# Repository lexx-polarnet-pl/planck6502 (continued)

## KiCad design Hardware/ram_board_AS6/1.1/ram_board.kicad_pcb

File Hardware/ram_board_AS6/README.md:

## Planck 6502 AS6 RAM board

This is a banked RAM board for the Planck 6502 computer (AS6C4008-55PCN version).

The original project used the IS61C5128AL-10TLI, which was hard for me to obtain and was an SMD version. The AS6 is THT, so the soldering process should be much easier.

## Revision History

| Version | Status | Changes |
| :---: | :---: | :--- |
| **1.1** | Work in progress | WE signal is now active only when CPU operates in RAM expansion card window |
| **1.0** | Partially working | Forked from original banked RAM project, replacing IS6 with AS6 |

**Version 1.0 doesn't work correctly, version 1.1 was not tested yet**

The address decoder in this version is used only for OE; therefore, the card works properly in READ mode. However, it is not used to control WE signals. As a result, if the CPU wants to write a value into a memory area that should be out of range for this card (e.g., $0080), the value will be stored both in main RAM (at $0080) and in banked RAM (at $8080).

How it should work:

When active, it gives access to a bank or RAM in the $8000-$BFFF address space.

To activate, store a byte with it's high bit set to the first register of the slot where it is placed.

For example 
lda #$80
sta $FFD0
will activate bank 0

There are 32 banks. You can choose which one is active by setting the first 5 bits of the data when storing to the first register. There is no way to get the currently active bank.

When the RAM card is active, it will respond to requests in the $8000 to $BFFF range instead of the ROM

lda #$8E
sta $FFD0
will activate the 14th bank

Setting the high bit to 0 will deactivate the banked RAM

For example the following code will deactivate the banked RAM and restore the ROM :

lda #0
sta $FFD0

<br />This documentation is licensed under a <a rel="license" href="http://creativecommons.org/licenses/by-sa/4.0/">Creative Commons Attribution-ShareAlike 4.0 International License</a>.

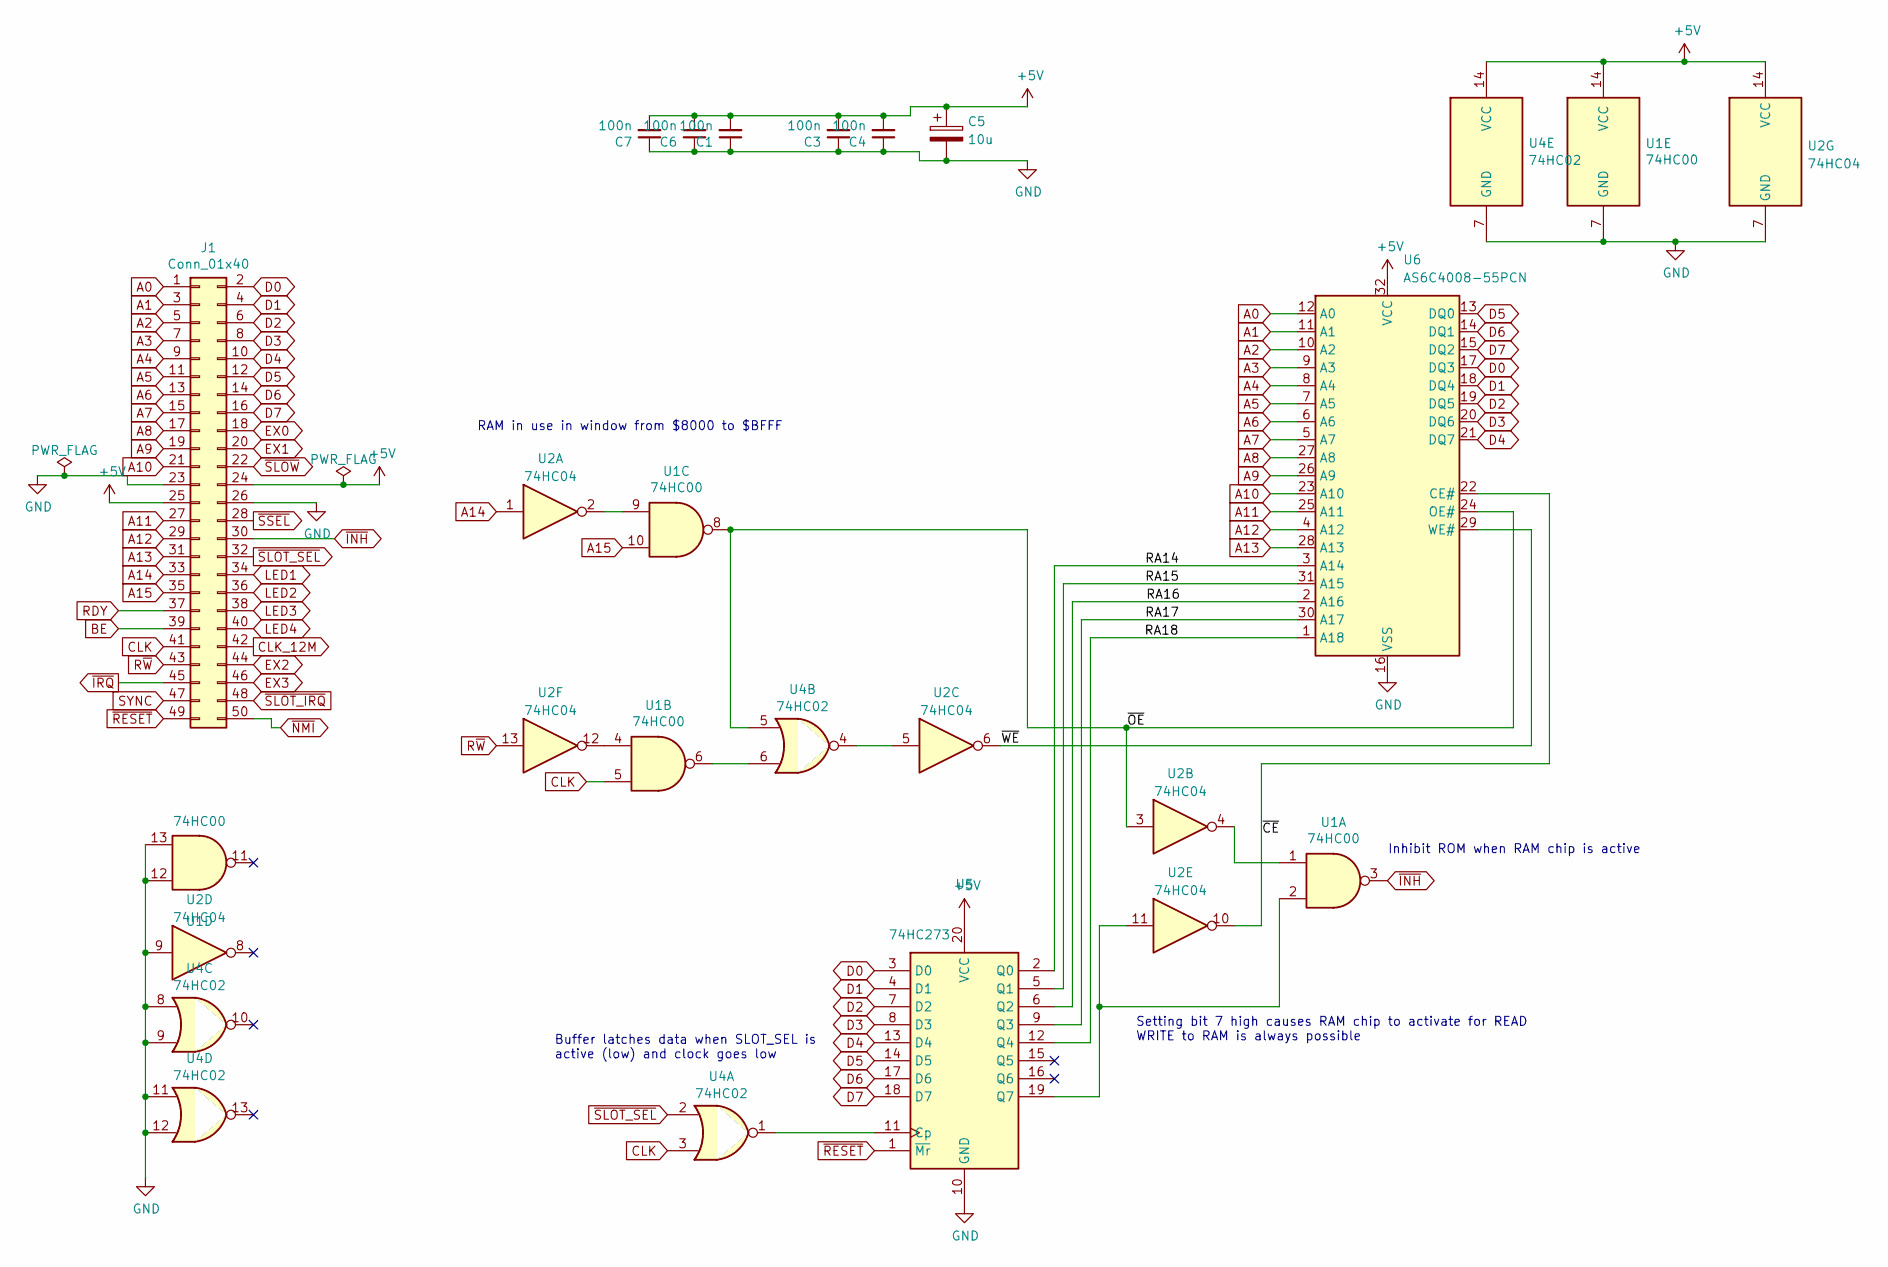
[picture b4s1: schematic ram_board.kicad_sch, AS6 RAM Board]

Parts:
C1, C3, C4, C6, C7: 100n; C_Disc_D4.3mm_W1.9mm_P5.00mm
C5: 10u; C_Radial_D5.0mm_H11.0mm_P2.00mm
J1: Conn_01x40; PinHeader_2x25_P2.54mm_Horizontal
U1: 74HC00; DIP-14_W7.62mm_Socket
U2: 74HC04; DIP-14_W7.62mm_Socket
U4: 74HC02; DIP-14_W7.62mm_Socket
U5: 74HC273; DIP-20_W7.62mm_Socket
U6: AS6C4008-55PCN; DIP-32_W15.24mm_Socket

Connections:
+5V: C1.2, C3.2, C4.2, C5.1, C6.2, C7.2, J1.24, J1.25, U1.14 (VCC), U2.14 (VCC), U4.14 (VCC), U5.20 (VCC), U6.32 (VCC)
/RA14: U5.2 (Q0), U6.3 (A14)
/RA15: U5.5 (Q1), U6.31 (A15)
/RA16: U5.6 (Q2), U6.2 (A16)
/RA17: U5.9 (Q3), U6.30 (A17)
/RA18: U5.12 (Q4), U6.1 (A18)
/~CE: U2.10, U6.22 (CE#)
/~OE: U1.8, U2.3, U4.5, U6.24 (OE#)
/~WE: U2.6, U6.29 (WE#)
A0: J1.1, U6.12 (A0)
A1: J1.3, U6.11 (A1)
A2: J1.5, U6.10 (A2)
A3: J1.7, U6.9 (A3)
A4: J1.9, U6.8 (A4)
A5: J1.11, U6.7 (A5)
A6: J1.13, U6.6 (A6)
A7: J1.15, U6.5 (A7)
A8: J1.17, U6.27 (A8)
A9: J1.19, U6.26 (A9)
A10: J1.21, U6.23 (A10)
A11: J1.27, U6.25 (A11)
A12: J1.29, U6.4 (A12)
A13: J1.31, U6.28 (A13)
A14: J1.33, U2.1
A15: J1.35, U1.10
BE: J1.39
CLK: J1.41, U1.5, U4.3
CLK_12M: J1.42
D0: J1.2, U5.3 (D0), U6.17 (DQ3)
D1: J1.4, U5.4 (D1), U6.18 (DQ4)
D2: J1.6, U5.7 (D2), U6.19 (DQ5)
D3: J1.8, U5.8 (D3), U6.20 (DQ6)
D4: J1.10, U5.13 (D4), U6.21 (DQ7)
D5: J1.12, U5.14 (D5), U6.13 (DQ0)
D6: J1.14, U5.17 (D6), U6.14 (DQ1)
D7: J1.16, U5.18 (D7), U6.15 (DQ2)
EX0: J1.18
EX1: J1.20
EX2: J1.44
EX3: J1.46
GND: C1.1, C3.1, C4.1, C5.2, C6.1, C7.1, J1.23, J1.26, U1.7 (GND), U1.12, U1.13, U2.7 (GND), U2.9, U4.7 (GND), U4.8, U4.9, U4.11, U4.12, U5.10 (GND), U6.16 (VSS)
LED1: J1.34
LED2: J1.36
LED3: J1.38
LED4: J1.40
unnamed: U1.1, U2.4
unnamed: U1.4, U2.12
unnamed: U1.6, U4.6
unnamed: U1.9, U2.2
unnamed: U2.5, U4.4
unnamed: U4.1, U5.11 (Cp)
unnamed: U1.2, U2.11, U5.19 (Q7)
RDY: J1.37
R~W: J1.43, U2.13
SYNC: J1.47
~INH: J1.30, U1.3
~IRQ: J1.45
~NMI: J1.50
~RESET: J1.49, U5.1 (~Mr)
~SLOT_IRQ: J1.48
~SLOT_SEL: J1.32, U4.2
~SLOW: J1.22
~SSEL: J1.28

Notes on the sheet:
Inhibit ROM when RAM chip is active
RAM in use in window from $8000 to $BFFF
Buffer latches data when SLOT_SEL is active (low) and clock goes low
Setting bit 7 high causes RAM chip to activate for READ WRITE to RAM is always possible

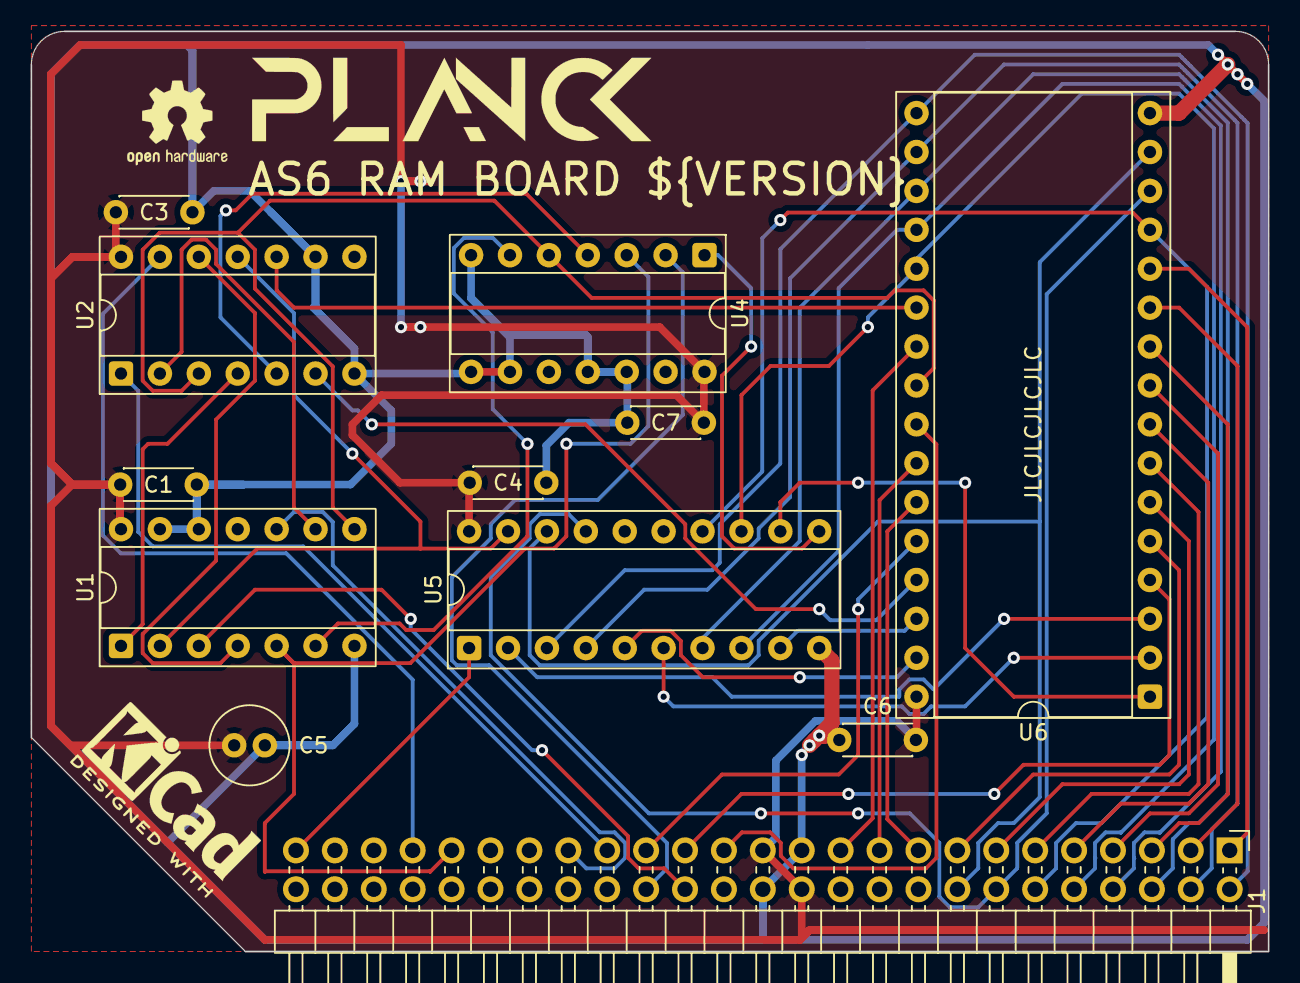
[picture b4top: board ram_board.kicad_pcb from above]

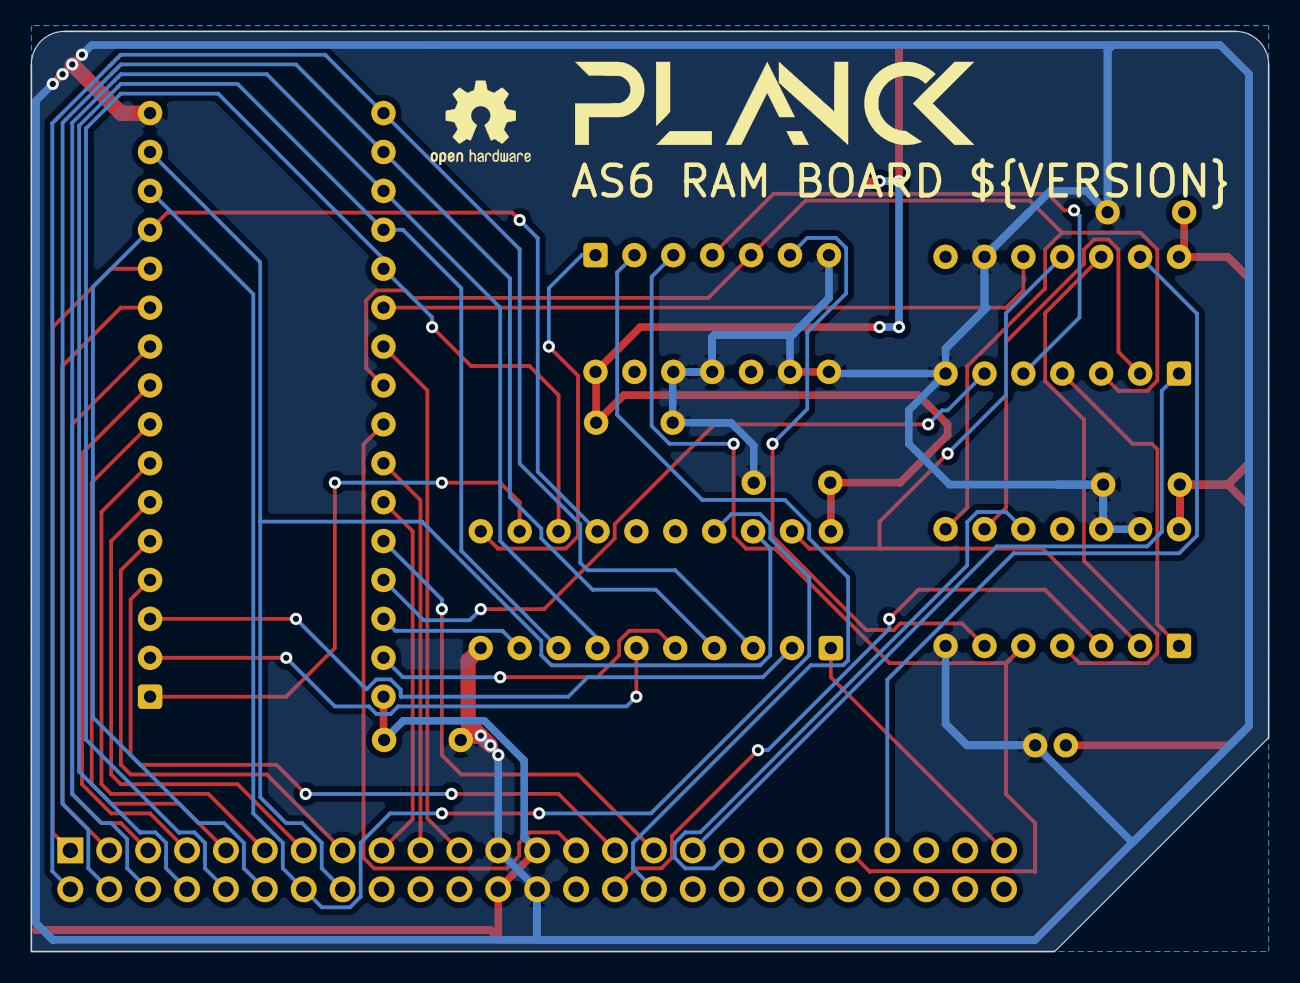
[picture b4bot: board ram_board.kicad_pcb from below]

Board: 2 copper layers, 80.8 x 60.1 mm, 16 parts (2 on the bottom side), 46 nets.

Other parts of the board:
LOGO, LOGO2: LOGO; logo
OSHW1, OSHW2: OSHW-Logo2_7.3x6mm_SilkScreen

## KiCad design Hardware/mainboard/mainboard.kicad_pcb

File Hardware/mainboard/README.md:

## Planck computer

This is a modified version of the original Planck mainboard, featuring a small addition that enables clock stretching for the serial interface.

Since the original design uses the W65C51 for serial communication and I had some R6551 chips on hand, I wanted to be able to use them instead. The pinout for both chips is identical; however, the R6551 can only run at a maximum of 2 MHz (depending on the version), so it cannot operate at the full CPU clock speed. With this additional jumper, it is possible to lower the clock frequency for the ACIA. Note that the main clock must be set to a maximum of 8 MHz, as the clock stretching circuit can divide the frequency by up to 4 times (meaning an original 12 MHz clock would yield 3 MHz during stretching, which is still too high for the R6551). The remainder of the design is identical to the original version.

## Revision History

| Version | Status | Changes |
| :---: | :---: | :--- |
| **1.4.9-Lexx** | Working | Forked from the project; added JP5 jumper to enable clock stretching for serial |

**This version is tested and working.**

Below is the original documentation excerpt:

This is a complete computer based on the Planck 6502 backplane.

It provides a 65c02 cPU, 32k of RAM, 32k of ROM and a serial port, as well as 6 expansion slots.

The board exceeds the original size specification of the original project (100 x 150mm instead of 100 x 100mm) but it seems that the cost will be similar (one more expensive board replaces 3 cheaper boards) as well as being more practical for some applications.

This computer can run absolutely stand alone when connected via the serial port. It can also accommodate 2 more expansion cards compared to the original backplane.

Here is a 3D view of the board:

You can [download the schematic](https://planck6502.com/fabrication/mainboard-schematic.pdf) and the [gerber files](https://planck6502.com/fabrication/mainboard-zip.zip)

[Documentation](https://planck6502.com/Hardware/io/)

<br />This documentation is licensed under a <a rel="license" href="http://creativecommons.org/licenses/by-sa/4.0/">Creative Commons Attribution-ShareAlike 4.0 International License</a>.

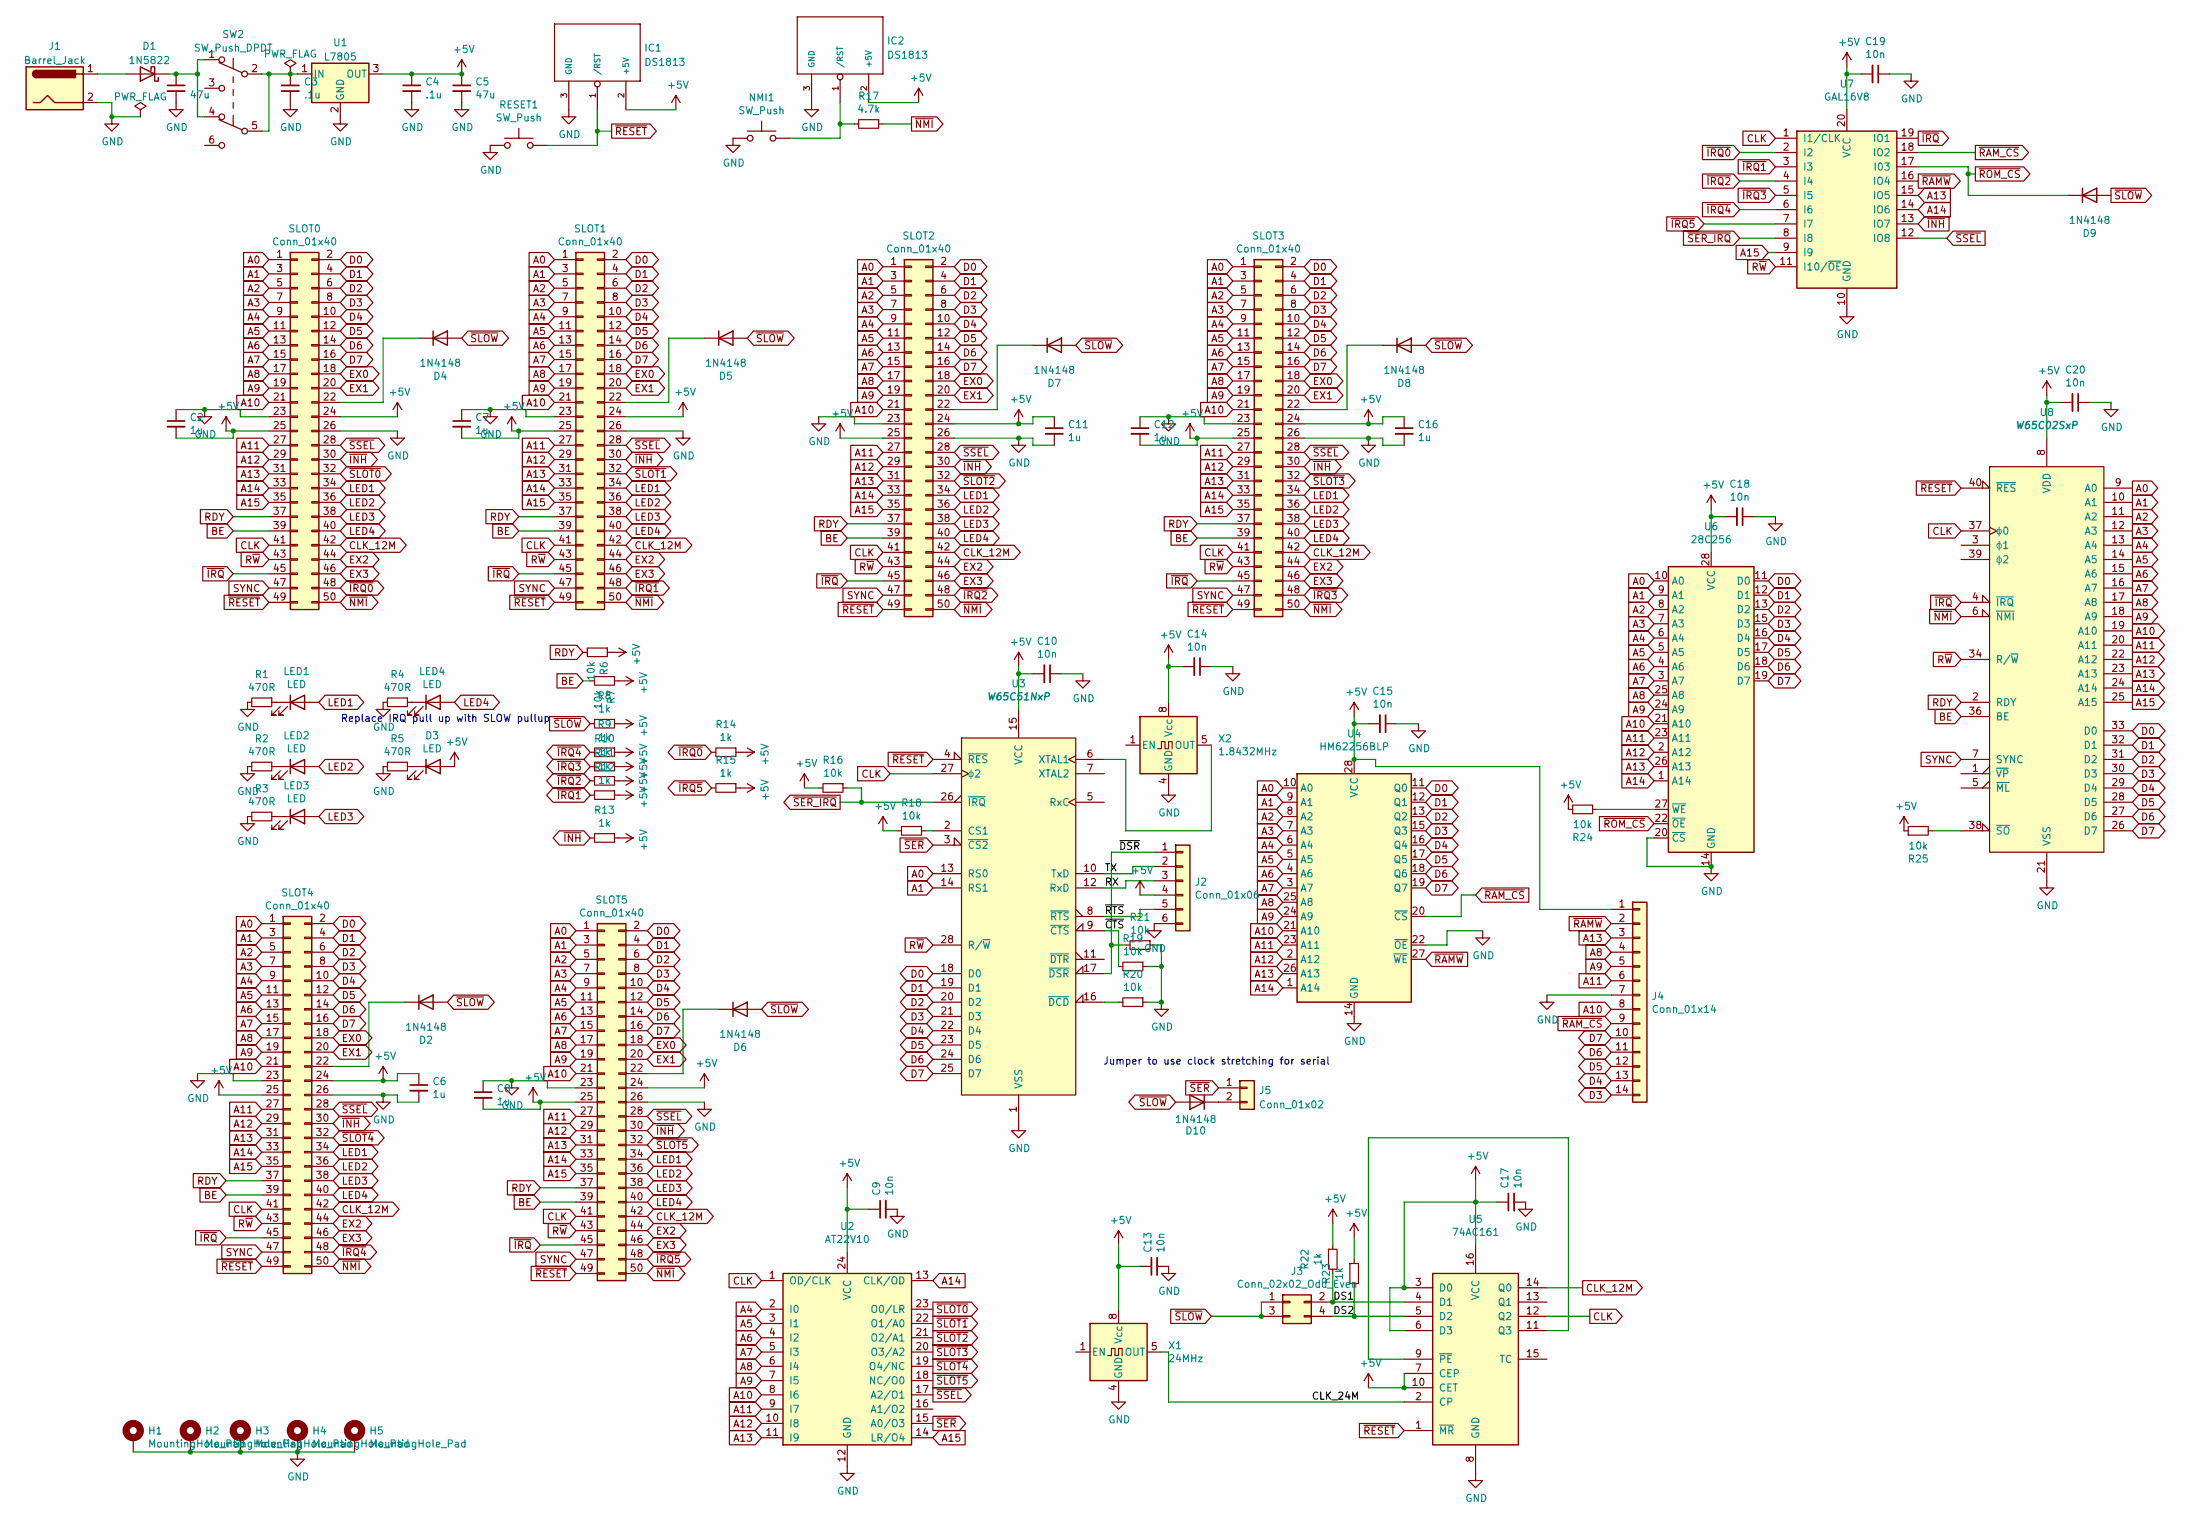
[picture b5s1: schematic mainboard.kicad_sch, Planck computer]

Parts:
C1, C5: 47u; CP_Radial_D4.0mm_P2.00mm
C2, C6, C7, C8, C11, C12, C16: 1u; C_Disc_D4.3mm_W1.9mm_P5.00mm
C3, C4: .1u; C_Disc_D4.3mm_W1.9mm_P5.00mm
C9, C10, C13, C14, C15, C17, C18, C19, C20: 10n; C_Disc_D4.3mm_W1.9mm_P5.00mm
D1: 1N5822; D_DO-201AD_P15.24mm_Horizontal
D2, D4, D5, D6, D7, D8, D9, D10: 1N4148; D_DO-35_SOD27_P7.62mm_Horizontal
D3: LED; LED_D3.0mm
H1, H2, H3, H4, H5: MountingHole_Pad; MountingHole_3.2mm_M3_Pad
IC1, IC2: DS1813; TO-92_Inline_Wide
J1: Barrel_Jack; BarrelJack_Horizontal
J2: Conn_01x06; PinSocket_1x06_P2.54mm_Vertical
J3: Conn_02x02_Odd_Even; PinHeader_2x02_P2.54mm_Vertical
J4: Conn_01x14; PinSocket_1x14_P2.54mm_Vertical
J5: Conn_01x02; PinHeader_1x02_P2.54mm_Vertical
LED1, LED2, LED3, LED4: LED; LED_D3.0mm
NMI1: SW_Push; SW_PUSH_6mm
R1, R2, R3, R4, R5: 470R; R_Axial_DIN0207_L6.3mm_D2.5mm_P7.62mm_Horizontal
R6, R7, R16, R18, R19, R20, R21, R24, R25: 10k; R_Axial_DIN0207_L6.3mm_D2.5mm_P7.62mm_Horizontal
R8, R9, R10, R11, R12, R13, R14, R15, R22, R23: 1k; R_Axial_DIN0207_L6.3mm_D2.5mm_P7.62mm_Horizontal
R17: 4.7k; R_Axial_DIN0207_L6.3mm_D2.5mm_P7.62mm_Horizontal
RESET1: SW_Push; SW_PUSH_6mm
SLOT0, SLOT1, SLOT2, SLOT3, SLOT4, SLOT5: Conn_01x40; PinSocket_2x25_P2.54mm_Vertical
SW2: SW_Push_DPDT; SW_E-Switch_EG1271_SPDT
U1: L7805; TO-220-3_Vertical
U2: AT22V10; DIP-24_W7.62mm_Socket
U3: W65C51NxP; DIP-28_W15.24mm_Socket
U4: HM62256BLP; DIP-28_W7.62mm_Socket
U5: 74AC161; DIP-16_W7.62mm_Socket
U6: 28C256; DIP-28_W15.24mm_Socket
U7: GAL16V8; DIP-20_W7.62mm_Socket
U8: W65C02SxP; DIP-40_W15.24mm_Socket
X1: 24MHz; Oscillator_DIP-8
X2: 1.8432MHz; Oscillator_DIP-8

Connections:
+5V: C2.2, C4.1, C5.1, C6.1, C7.2, C8.2, C9.1, C10.2, C11.1, C12.2, C13.1, C14.2, C15.2, C16.1, C17.1, C18.2, C19.2, C20.2, D3.2 (A), IC1.2 (+5V), IC2.2 (+5V), J2.4, J4.1, R6.1, R7.1, R8.1, R9.1, R10.1, R11.1, R12.1, R13.1, R14.1, R15.1, R16.2, R18.2, R22.1, R23.1, R24.1, R25.1, SLOT0.24, SLOT0.25, SLOT1.24, SLOT1.25, SLOT2.24, SLOT2.25, SLOT3.24, SLOT3.25, SLOT4.24, SLOT4.25, SLOT5.24, SLOT5.25, U1.3 (OUT), U2.24 (VCC), U3.15 (VCC), U4.28 (VCC), U5.3 (D0), U5.6 (D3), U5.7 (CEP), U5.10 (CET), U5.16 (VCC), U6.28 (VCC), U7.20 (VCC), U8.8 (VDD), X1.8 (Vcc), X2.8 (Vcc)
/CLK_24M: U5.2 (CP), X1.5 (OUT)
/DS1: J3.2, R22.2, U5.4 (D1)
/DS2: J3.4, R23.2, U5.5 (D2)
/RX: J2.3, U3.12 (RxD)
/TX: J2.2, U3.10 (TxD)
/~CTS: R19.2, U3.9 (~CTS)
/~DSR: J2.1, R21.2, U3.17 (~DSR)
/~RTS: J2.5, U3.8 (~RTS)
A0: SLOT0.1, SLOT1.1, SLOT2.1, SLOT3.1, SLOT4.1, SLOT5.1, U3.13 (RS0), U4.10 (A0), U6.10 (A0), U8.9 (A0)
A1: SLOT0.3, SLOT1.3, SLOT2.3, SLOT3.3, SLOT4.3, SLOT5.3, U3.14 (RS1), U4.9 (A1), U6.9 (A1), U8.10 (A1)
A2: SLOT0.5, SLOT1.5, SLOT2.5, SLOT3.5, SLOT4.5, SLOT5.5, U4.8 (A2), U6.8 (A2), U8.11 (A2)
A3: SLOT0.7, SLOT1.7, SLOT2.7, SLOT3.7, SLOT4.7, SLOT5.7, U4.7 (A3), U6.7 (A3), U8.12 (A3)
A4: SLOT0.9, SLOT1.9, SLOT2.9, SLOT3.9, SLOT4.9, SLOT5.9, U2.2 (I0), U4.6 (A4), U6.6 (A4), U8.13 (A4)
A5: SLOT0.11, SLOT1.11, SLOT2.11, SLOT3.11, SLOT4.11, SLOT5.11, U2.3 (I1), U4.5 (A5), U6.5 (A5), U8.14 (A5)
A6: SLOT0.13, SLOT1.13, SLOT2.13, SLOT3.13, SLOT4.13, SLOT5.13, U2.4 (I2), U4.4 (A6), U6.4 (A6), U8.15 (A6)
A7: SLOT0.15, SLOT1.15, SLOT2.15, SLOT3.15, SLOT4.15, SLOT5.15, U2.5 (I3), U4.3 (A7), U6.3 (A7), U8.16 (A7)
A8: J4.4, SLOT0.17, SLOT1.17, SLOT2.17, SLOT3.17, SLOT4.17, SLOT5.17, U2.6 (I4), U4.25 (A8), U6.25 (A8), U8.17 (A8)
A9: J4.5, SLOT0.19, SLOT1.19, SLOT2.19, SLOT3.19, SLOT4.19, SLOT5.19, U2.7 (I5), U4.24 (A9), U6.24 (A9), U8.18 (A9)
A10: J4.8, SLOT0.21, SLOT1.21, SLOT2.21, SLOT3.21, SLOT4.21, SLOT5.21, U2.8 (I6), U4.21 (A10), U6.21 (A10), U8.19 (A10)
A11: J4.6, SLOT0.27, SLOT1.27, SLOT2.27, SLOT3.27, SLOT4.27, SLOT5.27, U2.9 (I7), U4.23 (A11), U6.23 (A11), U8.20 (A11)
A12: SLOT0.29, SLOT1.29, SLOT2.29, SLOT3.29, SLOT4.29, SLOT5.29, U2.10 (I8), U4.2 (A12), U6.2 (A12), U8.22 (A12)
A13: J4.3, SLOT0.31, SLOT1.31, SLOT2.31, SLOT3.31, SLOT4.31, SLOT5.31, U2.11 (I9), U4.26 (A13), U6.26 (A13), U7.15 (IO5), U8.23 (A13)
A14: SLOT0.33, SLOT1.33, SLOT2.33, SLOT3.33, SLOT4.33, SLOT5.33, U2.13 (CLK/OD), U4.1 (A14), U6.1 (A14), U7.14 (IO6), U8.24 (A14)
A15: SLOT0.35, SLOT1.35, SLOT2.35, SLOT3.35, SLOT4.35, SLOT5.35, U2.14 (LR/O4), U7.9 (I9), U8.25 (A15)
BE: R7.2, SLOT0.39, SLOT1.39, SLOT2.39, SLOT3.39, SLOT4.39, SLOT5.39, U8.36 (BE)
CLK: SLOT0.41, SLOT1.41, SLOT2.41, SLOT3.41, SLOT4.41, SLOT5.41, U2.1 (OD/CLK), U3.27 (ϕ2), U5.12 (Q2), U7.1 (I1/CLK), U8.37 (ϕ0)
CLK_12M: SLOT0.42, SLOT1.42, SLOT2.42, SLOT3.42, SLOT4.42, SLOT5.42, U5.14 (Q0)
D0: SLOT0.2, SLOT1.2, SLOT2.2, SLOT3.2, SLOT4.2, SLOT5.2, U3.18 (D0), U4.11 (Q0), U6.11 (D0), U8.33 (D0)
D1: SLOT0.4, SLOT1.4, SLOT2.4, SLOT3.4, SLOT4.4, SLOT5.4, U3.19 (D1), U4.12 (Q1), U6.12 (D1), U8.32 (D1)
D2: SLOT0.6, SLOT1.6, SLOT2.6, SLOT3.6, SLOT4.6, SLOT5.6, U3.20 (D2), U4.13 (Q2), U6.13 (D2), U8.31 (D2)
D3: J4.14, SLOT0.8, SLOT1.8, SLOT2.8, SLOT3.8, SLOT4.8, SLOT5.8, U3.21 (D3), U4.15 (Q3), U6.15 (D3), U8.30 (D3)
D4: J4.13, SLOT0.10, SLOT1.10, SLOT2.10, SLOT3.10, SLOT4.10, SLOT5.10, U3.22 (D4), U4.16 (Q4), U6.16 (D4), U8.29 (D4)
D5: J4.12, SLOT0.12, SLOT1.12, SLOT2.12, SLOT3.12, SLOT4.12, SLOT5.12, U3.23 (D5), U4.17 (Q5), U6.17 (D5), U8.28 (D5)
D6: J4.11, SLOT0.14, SLOT1.14, SLOT2.14, SLOT3.14, SLOT4.14, SLOT5.14, U3.24 (D6), U4.18 (Q6), U6.18 (D6), U8.27 (D6)
D7: J4.10, SLOT0.16, SLOT1.16, SLOT2.16, SLOT3.16, SLOT4.16, SLOT5.16, U3.25 (D7), U4.19 (Q7), U6.19 (D7), U8.26 (D7)
EX0: SLOT0.18, SLOT1.18, SLOT2.18, SLOT3.18, SLOT4.18, SLOT5.18
EX1: SLOT0.20, SLOT1.20, SLOT2.20, SLOT3.20, SLOT4.20, SLOT5.20
EX2: SLOT0.44, SLOT1.44, SLOT2.44, SLOT3.44, SLOT4.44, SLOT5.44
EX3: SLOT0.46, SLOT1.46, SLOT2.46, SLOT3.46, SLOT4.46, SLOT5.46
GND: C1.2, C2.1, C3.2, C4.2, C5.2, C6.2, C7.1, C8.1, C9.2, C10.1, C11.2, C12.1, C13.2, C14.1, C15.1, C16.2, C17.2, C18.1, C19.1, C20.1, H1.1, H2.1, H3.1, H4.1, H5.1, IC1.3 (GND), IC2.3 (GND), J1.2, J2.6, J4.7, NMI1.1, R1.2, R2.2, R3.2, R4.2, R5.2, R19.1, R20.1, R21.1, RESET1.1, SLOT0.23, SLOT0.26, SLOT1.23, SLOT1.26, SLOT2.23, SLOT2.26, SLOT3.23, SLOT3.26, SLOT4.23, SLOT4.26, SLOT5.23, SLOT5.26, U1.2 (GND), U2.12 (GND), U3.1 (VSS), U4.14 (GND), U4.22 (~OE), U5.8 (GND), U6.14 (GND), U6.20 (~CS), U7.10 (GND), U8.21 (VSS), X1.4 (GND), X2.4 (GND)
LED1: LED1.2 (A), SLOT0.34, SLOT1.34, SLOT2.34, SLOT3.34, SLOT4.34, SLOT5.34
LED2: LED2.2 (A), SLOT0.36, SLOT1.36, SLOT2.36, SLOT3.36, SLOT4.36, SLOT5.36
LED3: LED3.2 (A), SLOT0.38, SLOT1.38, SLOT2.38, SLOT3.38, SLOT4.38, SLOT5.38
LED4: LED4.2 (A), SLOT0.40, SLOT1.40, SLOT2.40, SLOT3.40, SLOT4.40, SLOT5.40
unnamed: D1.2 (A), J1.1
unnamed: C1.1, D1.1 (K), SW2.1 (A), SW2.4 (A)
unnamed: D2.1 (K), SLOT4.22
unnamed: D3.1 (K), R5.1
unnamed: D4.1 (K), SLOT0.22
unnamed: D5.1 (K), SLOT1.22
unnamed: D6.1 (K), SLOT5.22
unnamed: D7.1 (K), SLOT2.22
unnamed: D8.1 (K), SLOT3.22
unnamed: D10.1 (K), J5.2
unnamed: IC2.1 (/RST), NMI1.2, R17.2
unnamed: LED1.1 (K), R1.1
unnamed: LED2.1 (K), R2.1
unnamed: LED3.1 (K), R3.1
unnamed: LED4.1 (K), R4.1
unnamed: C3.1, SW2.2 (B), SW2.5 (B), U1.1 (IN)
unnamed: R18.1, U3.2 (CS1)
unnamed: U3.6 (XTAL1), X2.5 (OUT)
unnamed: R20.2, U3.16 (~DCD)
unnamed: U5.9 (~PE), U5.11 (Q3)
unnamed: R24.2, U6.27 (~WE)
unnamed: R25.2, U8.38 (~SO)
RDY: R6.2, SLOT0.37, SLOT1.37, SLOT2.37, SLOT3.37, SLOT4.37, SLOT5.37, U8.2 (RDY)
R~W: SLOT0.43, SLOT1.43, SLOT2.43, SLOT3.43, SLOT4.43, SLOT5.43, U3.28 (R/~W), U7.11 (I10/~OE), U8.34 (R/~W)
SYNC: SLOT0.47, SLOT1.47, SLOT2.47, SLOT3.47, SLOT4.47, SLOT5.47, U8.7 (SYNC)
~INH: R13.2, SLOT0.30, SLOT1.30, SLOT2.30, SLOT3.30, SLOT4.30, SLOT5.30, U7.13 (IO7)
~IRQ0: R14.2, SLOT0.48, U7.2 (I2)
~IRQ1: R12.2, SLOT1.48, U7.3 (I3)
~IRQ2: R11.2, SLOT2.48, U7.4 (I4)
~IRQ3: R10.2, SLOT3.48, U7.5 (I5)
~IRQ4: R9.2, SLOT4.48, U7.6 (I6)
~IRQ5: R15.2, SLOT5.48, U7.7 (I7)
~IRQ: SLOT0.45, SLOT1.45, SLOT2.45, SLOT3.45, SLOT4.45, SLOT5.45, U7.19 (IO1), U8.4 (~IRQ)
~NMI: R17.1, SLOT0.50, SLOT1.50, SLOT2.50, SLOT3.50, SLOT4.50, SLOT5.50, U8.6 (~NMI)
~RAMW: J4.2, U4.27 (~WE), U7.16 (IO4)
~RAM_CS: J4.9, U4.20 (~CS), U7.18 (IO2)
~RESET: IC1.1 (/RST), RESET1.2, SLOT0.49, SLOT1.49, SLOT2.49, SLOT3.49, SLOT4.49, SLOT5.49, U3.4 (~RES), U5.1 (~MR), U8.40 (~RES)
~ROM_CS: D9.1 (K), U6.22 (~OE), U7.17 (I03)
~SER_IRQ: R16.1, U3.26 (~IRQ), U7.8 (I8)
~SER: J5.1, U2.15 (A0/O3), U3.3 (~CS2)
~SLOT0: SLOT0.32, U2.23 (O0/LR)
~SLOT1: SLOT1.32, U2.22 (O1/A0)
~SLOT2: SLOT2.32, U2.21 (O2/A1)
~SLOT3: SLOT3.32, U2.20 (O3/A2)
~SLOT4: SLOT4.32, U2.19 (O4/NC)
~SLOT5: SLOT5.32, U2.18 (NC/O0)
~SLOW: D2.2 (A), D4.2 (A), D5.2 (A), D6.2 (A), D7.2 (A), D8.2 (A), D9.2 (A), D10.2 (A), J3.1, J3.3, R8.2
~SSEL: SLOT0.28, SLOT1.28, SLOT2.28, SLOT3.28, SLOT4.28, SLOT5.28, U2.17 (A2/O1), U7.12 (IO8)

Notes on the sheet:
Jumper to use clock stretching for serial
Replace IRQ pull up with SLOW pullup

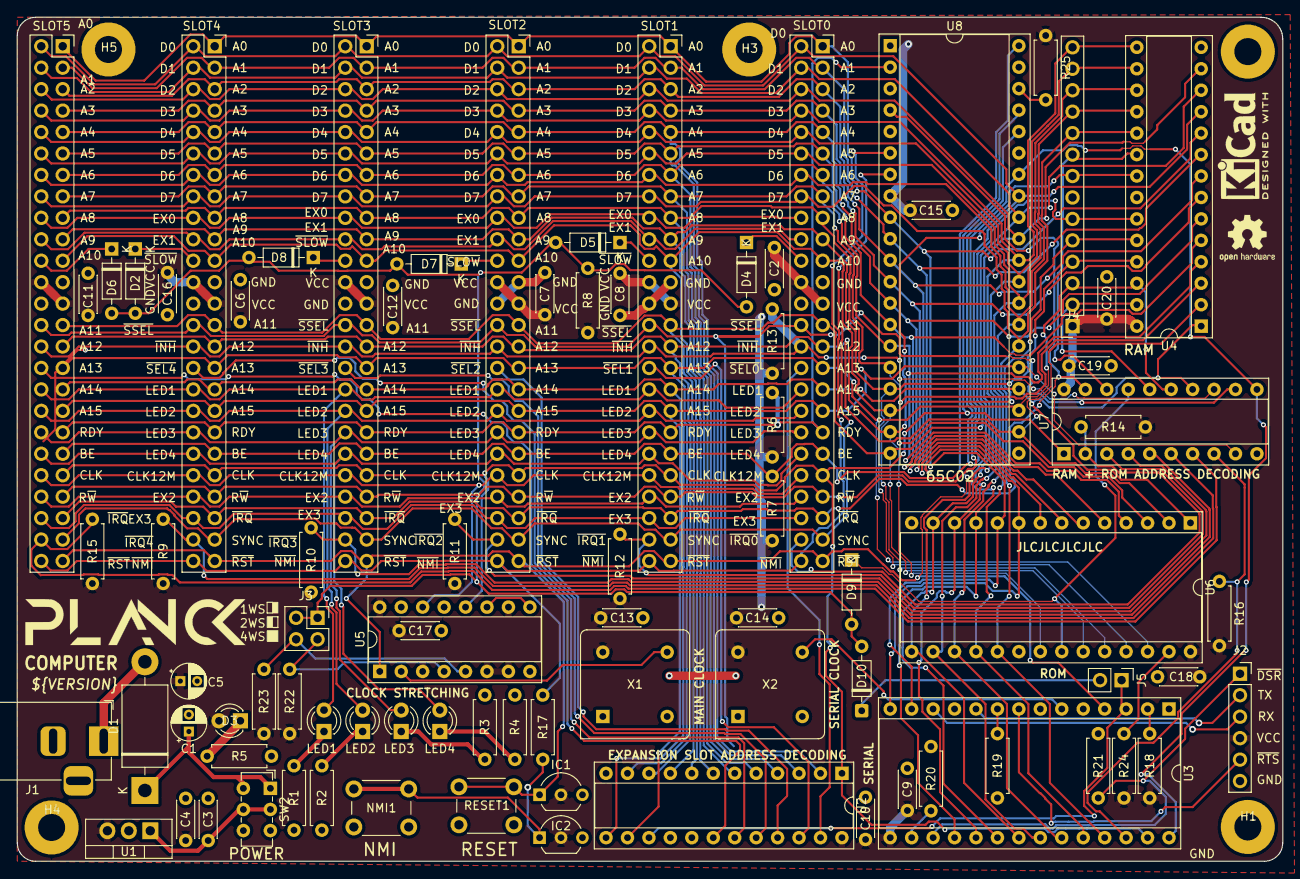
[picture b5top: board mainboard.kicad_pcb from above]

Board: 2 copper layers, 149.9 x 99.9 mm, 90 parts (0 on the bottom side), 93 nets.

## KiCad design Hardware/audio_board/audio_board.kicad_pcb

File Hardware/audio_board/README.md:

## Planck 6502 audio card

This is an audio card for the Planck 6502 computer.

It is a major modification of the original Planck sound card, which was based solely on the OPL2 chip.

## Revision History

| Version | Status | Changes |
| :---: | :---: | :--- |
| **1.0** | Tested and working | Initial release |

**This version is tested and working.**

This card integrates two sound chips on a single board. The first is the TLC7226CN, a 4-channel, 8-bit DAC (Digital-to-Analog Converter) that enables the Planck to play 8-bit samples. The four independent audio channels are paired into left and right channel outputs, allowing for true stereo sound playback. The second chip is the Yamaha YM3812 (OPL2), which handles FM-based synthesis. This chip was famously used in the AdLib and early Sound Blaster sound cards.

See an [example of the card's capabilities](https://youtube.com/shorts/hnlIDgAt0dc?si=HoMWPFpHYaL4QCAE).

The memory mapping for this card is as follows:

```asm
DAC_RIGHT_1 = SOUND_CARD_PORT + 0
DAC_LEFT_1  = SOUND_CARD_PORT + 1
DAC_LEFT_2  = SOUND_CARD_PORT + 2
DAC_RIGHT_2 = SOUND_CARD_PORT + 3

OPL_ADDR = SOUND_CARD_PORT + 8
OPL_DATA = SOUND_CARD_PORT + 9
```

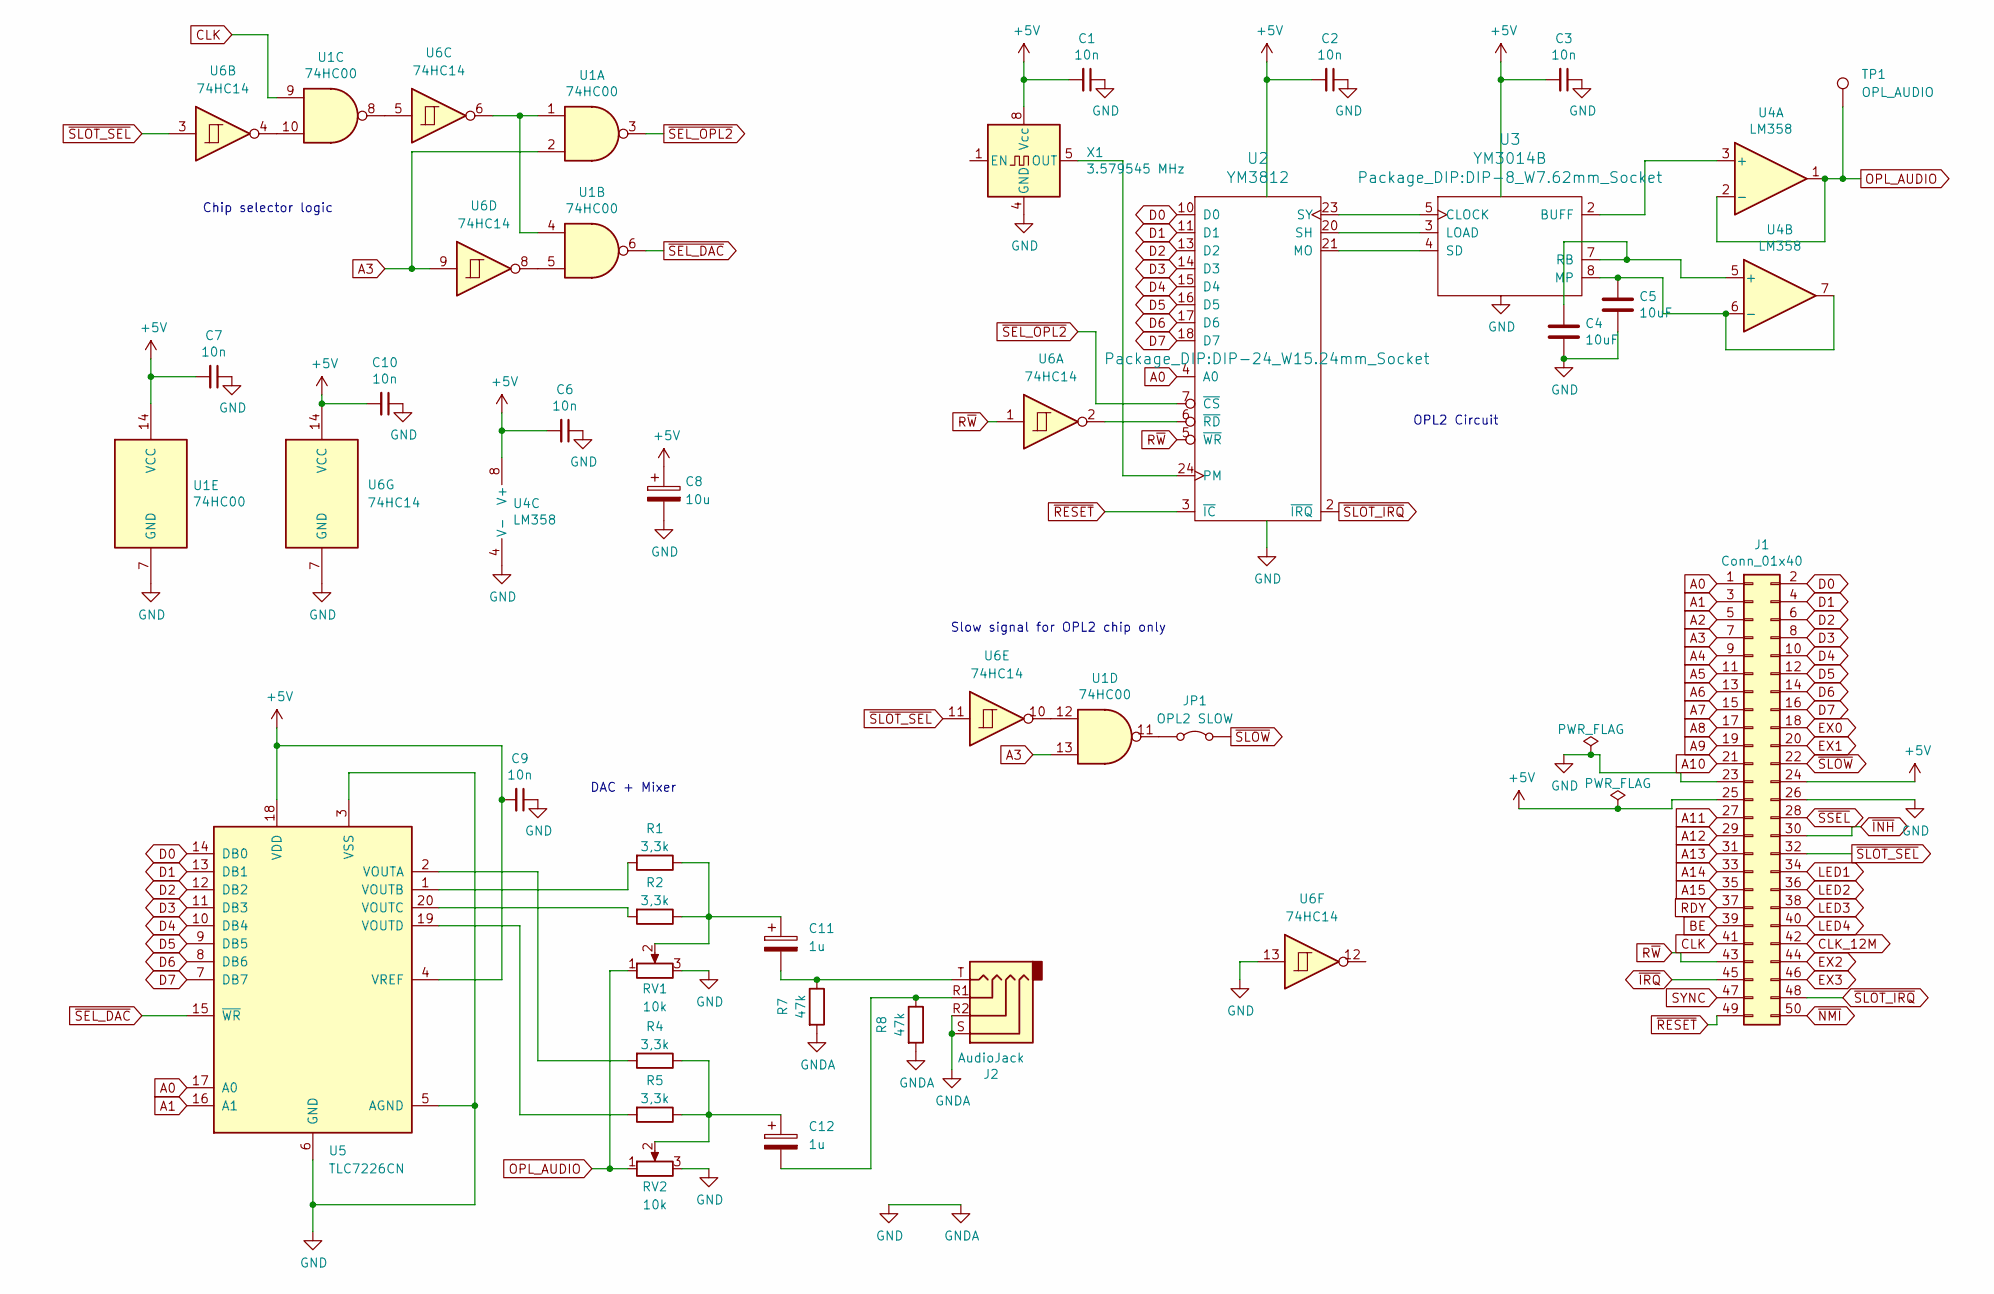
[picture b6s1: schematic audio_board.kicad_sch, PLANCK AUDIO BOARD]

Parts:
C1, C2, C3, C6, C7, C9, C10: 10n; C_Disc_D4.3mm_W1.9mm_P5.00mm
C4, C5: 10uF; C_Disc_D4.3mm_W1.9mm_P5.00mm
C8: 10u; CP_Radial_D5.0mm_P2.50mm
C11, C12: 1u; CP_Radial_D5.0mm_P2.50mm
J1: Conn_01x40; PinHeader_2x25_P2.54mm_Horizontal
J2: AudioJack; TRRS-PJ-320A-no-Fmask
JP1: OPL2 SLOW; TestPoint_2Pads_Pitch2.54mm_Drill0.8mm
R1, R2, R4, R5: 3,3k; R_Axial_DIN0207_L6.3mm_D2.5mm_P10.16mm_Horizontal
R7, R8: 47k; R_Axial_DIN0207_L6.3mm_D2.5mm_P10.16mm_Horizontal
RV1, RV2: 10k; Potentiometer_Runtron_RM-065_Vertical
TP1: OPL_AUDIO; Pin_D0.7mm_L6.5mm_W1.8mm_FlatFork
U1: 74HC00; DIP-14_W7.62mm_Socket
U2: YM3812; DIP-24_W15.24mm_Socket
U3: YM3014B; DIP-8_W7.62mm_Socket
U4: LM358; DIP-8_W7.62mm_Socket
U5: TLC7226CN; DIP-20_W7.62mm_Socket
U6: 74HC14; DIP-14_W7.62mm_Socket
X1: 3.579545 MHz; Oscillator_DIP-8

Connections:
+5V: C1.2, C2.2, C3.2, C6.2, C7.2, C8.1, C9.2, C10.2, J1.24, J1.25, U1.14 (VCC), U2.1 (VCC), U3.1 (VCC), U4.8 (V+), U5.4 (VREF), U5.18 (VDD), U6.14 (VCC), X1.8 (Vcc)
A0: J1.1, U2.4 (A0), U5.17 (A0)
A1: J1.3, U5.16 (A1)
A2: J1.5
A3: J1.7, U1.2, U1.13, U6.9
A4: J1.9
A5: J1.11
A6: J1.13
A7: J1.15
A8: J1.17
A9: J1.19
A10: J1.21
A11: J1.27
A12: J1.29
A13: J1.31
A14: J1.33
A15: J1.35
BE: J1.39
CLK: J1.41, U1.9
CLK_12M: J1.42
D0: J1.2, U2.10 (D0), U5.14 (DB0)
D1: J1.4, U2.11 (D1), U5.13 (DB1)
D2: J1.6, U2.13 (D2), U5.12 (DB2)
D3: J1.8, U2.14 (D3), U5.11 (DB3)
D4: J1.10, U2.15 (D4), U5.10 (DB4)
D5: J1.12, U2.16 (D5), U5.9 (DB5)
D6: J1.14, U2.17 (D6), U5.8 (DB6)
D7: J1.16, U2.18 (D7), U5.7 (DB7)
EX0: J1.18
EX1: J1.20
EX2: J1.44
EX3: J1.46
GND: C1.1, C2.1, C3.1, C4.2, C5.2, C6.1, C7.1, C8.2, C9.1, C10.1, J1.23, J1.26, J2.R2, J2.S, R7.2, R8.2, RV1.3, RV2.3, U1.7 (GND), U2.12 (GND), U3.6 (GND), U4.4 (V-), U5.3 (VSS), U5.5 (AGND), U5.6 (GND), U6.7 (GND), U6.13, X1.4 (GND)
LED1: J1.34
LED2: J1.36
LED3: J1.38
LED4: J1.40
unnamed: C11.1, R1.1, R2.1, RV1.2
unnamed: C11.2, J2.T, R7.1
unnamed: C12.1, R4.1, R5.1, RV2.2
unnamed: C12.2, J2.R1, R8.1
unnamed 41: JP1.1 (A), U1.11; also elsewhere on the board
unnamed: U1.1, U1.4, U6.6
unnamed: U1.5, U6.8
unnamed: U1.8, U6.5
unnamed: U1.10, U6.4
unnamed: U1.12, U6.10
unnamed: U2.21 (MO), U3.4 (SD)
unnamed: U2.24 (PM), X1.5 (OUT)
unnamed: U2.20 (SH), U3.3 (LOAD)
unnamed: U2.23 (SY), U3.5 (CLOCK)
unnamed: U2.6 (~RD), U6.2
unnamed: U3.2 (BUFF), U4.3 (+)
unnamed: C5.1, U3.8 (MP), U4.6 (-), U4.7
unnamed: C4.1, U3.7 (RB), U4.5 (+)
unnamed: R4.2, U5.2 (VOUTA)
unnamed: R1.2, U5.1 (VOUTB)
unnamed: R2.2, U5.20 (VOUTC)
unnamed: R5.2, U5.19 (VOUTD)
OPL_AUDIO: RV1.1, RV2.1, TP1.1 (1_1), U4.1, U4.2 (-)
RDY: J1.37
R~W: J1.43, U2.5 (~WR), U6.1
SYNC: J1.47
~INH: J1.30
~IRQ: J1.45
~NMI: J1.50
~RESET: J1.49, U2.3 (~IC)
~SEL_DAC: U1.6, U5.15 (~WR)
~SEL_OPL2: U1.3, U2.7 (~CS)
~SLOT_IRQ: J1.48, U2.2 (~IRQ)
~SLOT_SEL: J1.32, U6.3, U6.11
~SLOW: J1.22, JP1.2 (B); also elsewhere on the board
~SSEL: J1.28

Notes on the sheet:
Slow signal for OPL2 chip only
OPL2 Circuit
DAC + Mixer
Chip selector logic
